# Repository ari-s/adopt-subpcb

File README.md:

Adopt existing designs into a kicad_pcb to reuse pcb layouts for function groups or to have multiple instance of a group

You have the PCB design for a buck regulator and the surounding parts or some analog filter designed. Now you want to reuse it. Unfortunately kicad / pcbnew makes it borderline impossible to integrate / reuse PCB designs - there's no function to include a hierarchical PCB like there is for hierarchical sheets in eeeschema. adopt_subpcb.py to the rescue:

Example
===

```
  # cd test-rc; python3 ../adopt_subpcb.py \
    -o /tmp/test.kicad_pcb \
    test-rc/2x-rc.kicad_pcb \
    test-rc/rc.kicad_pcb \
    test-rc/2x-rc.net \
    0 0 0 -2.5
```
Howto structure your kicad project
===

sub(pcb,schematic) is the pcb-design and corresponding schematic you want to reuse

| Structure    | Example |     |
| ------------ | --------| --- |
| subschematic | rc.sch  |     |
| subpcb       | rc.kicad_pcb| pcb design created with the standard kicad workflow for the subpcb |
| mainschematic| 2x-rc.sch   | mainschematic includes subschematic as hierarchical sheet |
| - hierarchical sheets| - rc: rc.sch | instance 1: hierarchical sheet created with rc.sch as filename and rc as sheet name|
| - ...        | - rc2: rc.sch | instance 2 of same subschematic |
| netlist      | 2x-rc.net| netlist of the complete schematics |
| pcbdesign    | 2x-rc.kicad_pcb | the pcb design featuring subpcb |

before running `adopt_subpcb.py`, you have to open pcbnew for the pcbdesign and read the netlist, resulting in your design being populated with the parts. `child_module_ts` moves the parts and imports traces and vias from the subpcb, thereby adopting that design.

- You have to specify coordinates at which the origin of the subpcb is inserted into your pcb design.
- If your design features multiple instances of the same subpcb, all instances or the one you specify with --instance are adapted

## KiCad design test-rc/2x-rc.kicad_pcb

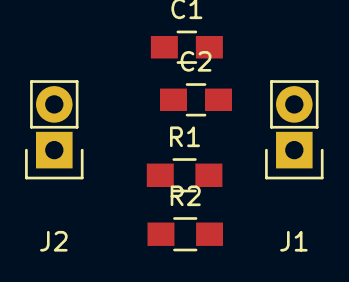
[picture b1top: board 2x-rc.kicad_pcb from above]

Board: 2 copper layers, 6 parts (0 on the bottom side), 5 nets, no tracks yet.

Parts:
C1, C2: C; C_0805_HandSoldering
J1, J2: CONN_01X02; Pin_Header_Straight_1x02
R1, R2: R; R_0805_HandSoldering

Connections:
/rc2/In: J1.2, R2.2
/rc2/Out: C2.1, J2.2, R2.1
/rc/In: J1.1, R1.2
/rc/Out: C1.1, J2.1, R1.1
GND: C1.2, C2.2

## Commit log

2017-09-17 basic functionality working
2017-09-17 "documentation and cleanup"
2017-09-17 add the test circuit
2017-09-17 gitignore
2017-09-17 renamed the space out of test-rc files
2017-09-17 add argparse functionality
2017-09-17 renamed panelize.py to adopt_subpcb.py
2017-09-17 deepcopy to avoid messing up child tree, deepcopy should be avoidable
2017-09-17 add readme with screenshots
